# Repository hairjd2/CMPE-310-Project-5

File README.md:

# CMPE-310-Project-5
## Created by Seth Ellis and John Hair (CMPE-306 Failers)

### Design

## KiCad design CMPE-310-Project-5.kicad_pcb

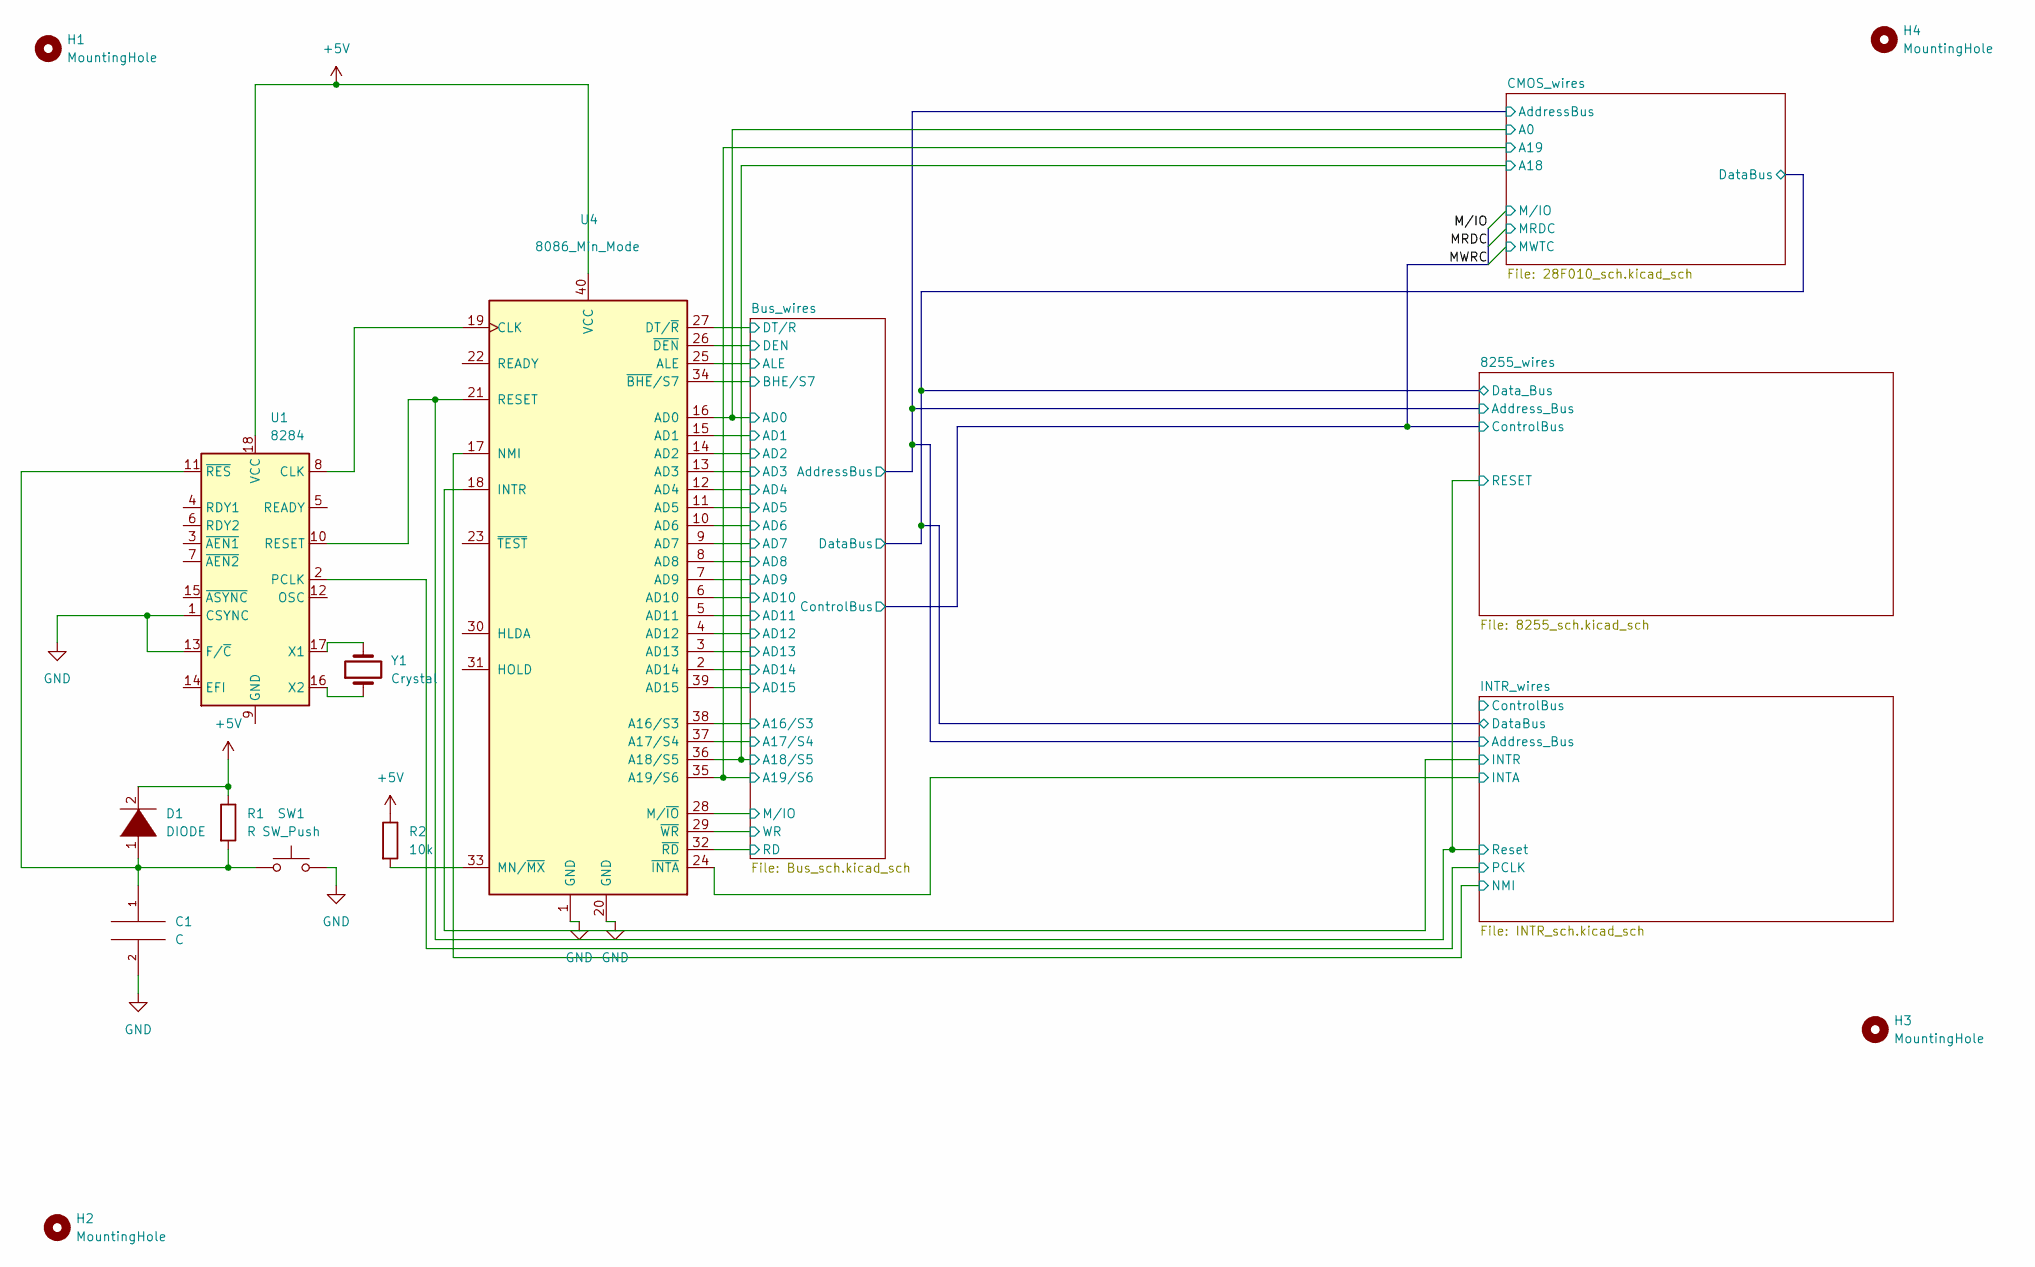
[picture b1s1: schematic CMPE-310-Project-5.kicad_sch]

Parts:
C1: C; CP_Elec_3x5.3
D1: DIODE; D_0201_0603Metric
H1, H2, H3, H4: MountingHole
R1: R; R_0201_0603Metric
R2: 10k; R_0201_0603Metric
SW1: SW_Push; SW_Cherry_MX_1.00u_PCB
U1: 8284; DIP-18_W7.62mm
U4: 8086_Min_Mode; DIP-40_W15.24mm
Y1: Crystal; Crystal_AT310_D3.0mm_L10.0mm_Horizontal

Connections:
+5V: D1.2 (A), R1.1, R2.1, U1.18 (VCC), U4.40 (VCC); also elsewhere on the board
/8255_wires/RESET: U1.10 (RESET), U4.21 (RESET); also elsewhere on the board
/Bus_wires/A16/S3: U4.38 (A16/S3); also elsewhere on the board
/Bus_wires/A17/S4: U4.37 (A17/S4); also elsewhere on the board
/Bus_wires/AD1: U4.15 (AD1); also elsewhere on the board
/Bus_wires/AD2: U4.14 (AD2); also elsewhere on the board
/Bus_wires/AD3: U4.13 (AD3); also elsewhere on the board
/Bus_wires/AD4: U4.12 (AD4); also elsewhere on the board
/Bus_wires/AD5: U4.11 (AD5); also elsewhere on the board
/Bus_wires/AD6: U4.10 (AD6); also elsewhere on the board
/Bus_wires/AD7: U4.9 (AD7); also elsewhere on the board
/Bus_wires/AD8: U4.8 (AD8); also elsewhere on the board
/Bus_wires/AD9: U4.7 (AD9); also elsewhere on the board
/Bus_wires/AD10: U4.6 (AD10); also elsewhere on the board
/Bus_wires/AD11: U4.5 (AD11); also elsewhere on the board
/Bus_wires/AD12: U4.4 (AD12); also elsewhere on the board
/Bus_wires/AD13: U4.3 (AD13); also elsewhere on the board
/Bus_wires/AD14: U4.2 (AD14); also elsewhere on the board
/Bus_wires/AD15: U4.39 (AD15); also elsewhere on the board
/Bus_wires/ALE: U4.25 (ALE); also elsewhere on the board
/Bus_wires/BHE/S7: U4.34 (~BHE/S7); also elsewhere on the board
/Bus_wires/DEN: U4.26 (~DEN); also elsewhere on the board
/Bus_wires/DT/R: U4.27 (DT/~R); also elsewhere on the board
/Bus_wires/RD: U4.32 (~RD); also elsewhere on the board
/Bus_wires/WR: U4.29 (~WR); also elsewhere on the board
/CMOS_wires/A0: U4.16 (AD0); also elsewhere on the board
/CMOS_wires/A18: U4.36 (A18/S5); also elsewhere on the board
/CMOS_wires/A19: U4.35 (A19/S6); also elsewhere on the board
/INTR_wires/INTA: U4.24 (~INTA); also elsewhere on the board
/INTR_wires/INTR: U4.18 (INTR); also elsewhere on the board
/INTR_wires/NMI: U4.17 (NMI); also elsewhere on the board
/INTR_wires/PCLK: U1.2 (PCLK); also elsewhere on the board
/MRDC: U4.28 (M/~IO); also elsewhere on the board
GND: C1.2, SW1.2, U1.1 (CSYNC), U1.13 (F/~C), U4.1 (GND), U4.20 (GND); also elsewhere on the board
unnamed: C1.1, D1.1 (K), R1.2, SW1.1, U1.11 (~RES)
unnamed: R2.2, U4.33 (MN/~MX)
unnamed: U1.8 (CLK), U4.19 (CLK)
unnamed: U1.16 (X2), Y1.1
unnamed: U1.17 (X1), Y1.2

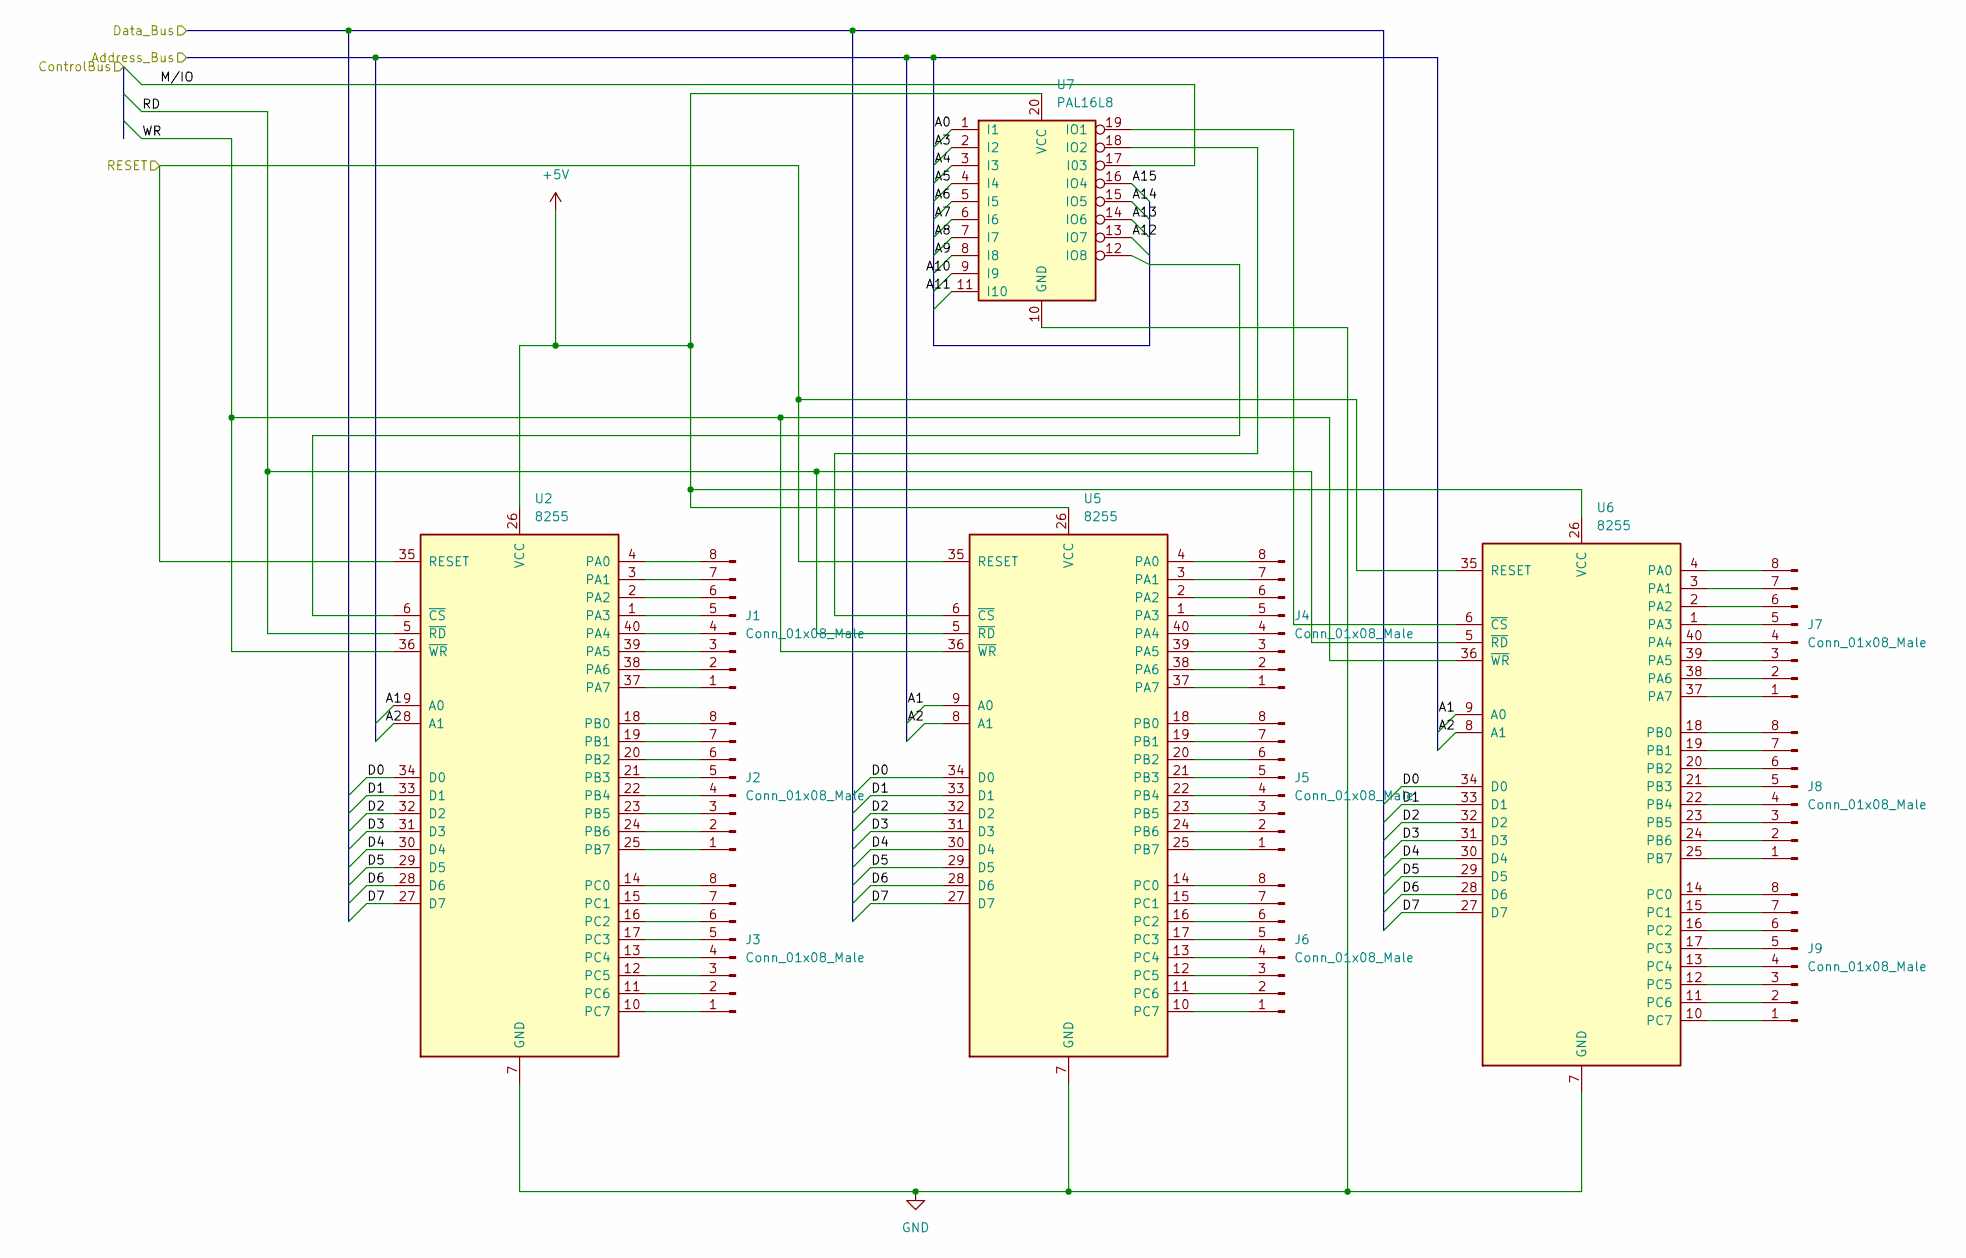
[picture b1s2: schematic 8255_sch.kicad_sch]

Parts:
J1, J2, J3, J4, J5, J6, J7, J8, J9: Conn_01x08_Male; Harwin_M20-89008xx_1x08_P2.54mm_Horizontal
U2, U5, U6: 8255; DIP-40_W15.24mm
U7: PAL16L8; DIP-20_W7.62mm

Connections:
+5V: U2.26 (VCC), U5.26 (VCC), U6.26 (VCC), U7.20 (VCC); also elsewhere on the board
/8255_wires/A0: U7.1 (I1)
/8255_wires/A1: U5.9 (A0), U6.9 (A0)
/8255_wires/A2: U5.8 (A1), U6.8 (A1)
/8255_wires/A3: U7.2 (I2)
/8255_wires/A4: U7.3 (I3)
/8255_wires/A5: U7.4 (I4)
/8255_wires/A6: U7.5 (I5)
/8255_wires/A7: U7.6 (I6)
/8255_wires/A8: U7.7 (I7)
/8255_wires/A9: U7.8 (I8)
/8255_wires/A10: U7.9 (I9)
/8255_wires/A11: U7.11 (I10)
/8255_wires/A12: U7.13 (IO7)
/8255_wires/A13: U7.14 (IO6)
/8255_wires/A14: U7.15 (IO5)
/8255_wires/A15: U7.16 (IO4)
/8255_wires/D0: U2.34 (D0), U5.34 (D0), U6.34 (D0)
/8255_wires/D1: U2.33 (D1), U5.33 (D1), U6.33 (D1)
/8255_wires/D2: U2.32 (D2), U5.32 (D2), U6.32 (D2)
/8255_wires/D3: U2.31 (D3), U5.31 (D3), U6.31 (D3)
/8255_wires/D4: U2.30 (D4), U5.30 (D4), U6.30 (D4)
/8255_wires/D5: U2.29 (D5), U5.29 (D5), U6.29 (D5)
/8255_wires/D6: U2.28 (D6), U5.28 (D6), U6.28 (D6)
/8255_wires/D7: U2.27 (D7), U5.27 (D7), U6.27 (D7)
/8255_wires/M/IO: U7.17 (I03)
/8255_wires/RD: U2.5 (~RD), U5.5 (~RD), U6.5 (~RD)
/8255_wires/RESET: U2.35 (RESET), U5.35 (RESET), U6.35 (RESET); also elsewhere on the board
/8255_wires/WR: U2.36 (~WR), U5.36 (~WR), U6.36 (~WR)
GND: U2.7 (GND), U5.7 (GND), U6.7 (GND), U7.10 (GND); also elsewhere on the board
unnamed: J1.1, U2.37 (PA7)
unnamed: J1.2, U2.38 (PA6)
unnamed: J1.3, U2.39 (PA5)
unnamed: J1.4, U2.40 (PA4)
unnamed: J1.5, U2.1 (PA3)
unnamed: J1.6, U2.2 (PA2)
unnamed: J1.7, U2.3 (PA1)
unnamed: J1.8, U2.4 (PA0)
unnamed: J2.1, U2.25 (PB7)
unnamed: J2.2, U2.24 (PB6)
unnamed: J2.3, U2.23 (PB5)
unnamed: J2.4, U2.22 (PB4)
unnamed: J2.5, U2.21 (PB3)
unnamed: J2.6, U2.20 (PB2)
unnamed: J2.7, U2.19 (PB1)
unnamed: J2.8, U2.18 (PB0)
unnamed: J3.1, U2.10 (PC7)
unnamed: J3.2, U2.11 (PC6)
unnamed: J3.3, U2.12 (PC5)
unnamed: J3.4, U2.13 (PC4)
unnamed: J3.5, U2.17 (PC3)
unnamed: J3.6, U2.16 (PC2)
unnamed: J3.7, U2.15 (PC1)
unnamed: J3.8, U2.14 (PC0)
unnamed: J4.1, U5.37 (PA7)
unnamed: J4.2, U5.38 (PA6)
unnamed: J4.3, U5.39 (PA5)
unnamed: J4.4, U5.40 (PA4)
unnamed: J4.5, U5.1 (PA3)
unnamed: J4.6, U5.2 (PA2)
unnamed: J4.7, U5.3 (PA1)
unnamed: J4.8, U5.4 (PA0)
unnamed: J5.1, U5.25 (PB7)
unnamed: J5.2, U5.24 (PB6)
unnamed: J5.3, U5.23 (PB5)
unnamed: J5.4, U5.22 (PB4)
unnamed: J5.5, U5.21 (PB3)
unnamed: J5.6, U5.20 (PB2)
unnamed: J5.7, U5.19 (PB1)
unnamed: J5.8, U5.18 (PB0)
unnamed: J6.1, U5.10 (PC7)
unnamed: J6.2, U5.11 (PC6)
unnamed: J6.3, U5.12 (PC5)
unnamed: J6.4, U5.13 (PC4)
unnamed: J6.5, U5.17 (PC3)
unnamed: J6.6, U5.16 (PC2)
unnamed: J6.7, U5.15 (PC1)
unnamed: J6.8, U5.14 (PC0)
unnamed: J7.1, U6.37 (PA7)
unnamed: J7.2, U6.38 (PA6)
unnamed: J7.3, U6.39 (PA5)
unnamed: J7.4, U6.40 (PA4)
unnamed: J7.5, U6.1 (PA3)
unnamed: J7.6, U6.2 (PA2)
unnamed: J7.7, U6.3 (PA1)
unnamed: J7.8, U6.4 (PA0)
unnamed: J8.1, U6.25 (PB7)
unnamed: J8.2, U6.24 (PB6)
unnamed: J8.3, U6.23 (PB5)
unnamed: J8.4, U6.22 (PB4)
unnamed: J8.5, U6.21 (PB3)
unnamed: J8.6, U6.20 (PB2)
unnamed: J8.7, U6.19 (PB1)
unnamed: J8.8, U6.18 (PB0)
unnamed: J9.1, U6.10 (PC7)
unnamed: J9.2, U6.11 (PC6)
unnamed: J9.3, U6.12 (PC5)
unnamed: J9.4, U6.13 (PC4)
unnamed: J9.5, U6.17 (PC3)
unnamed: J9.6, U6.16 (PC2)
unnamed: J9.7, U6.15 (PC1)
unnamed: J9.8, U6.14 (PC0)
unnamed: U2.6 (~CS), U7.12 (IO8)
unnamed: U5.6 (~CS), U7.18 (IO2)
unnamed: U6.6 (~CS), U7.19 (IO1)

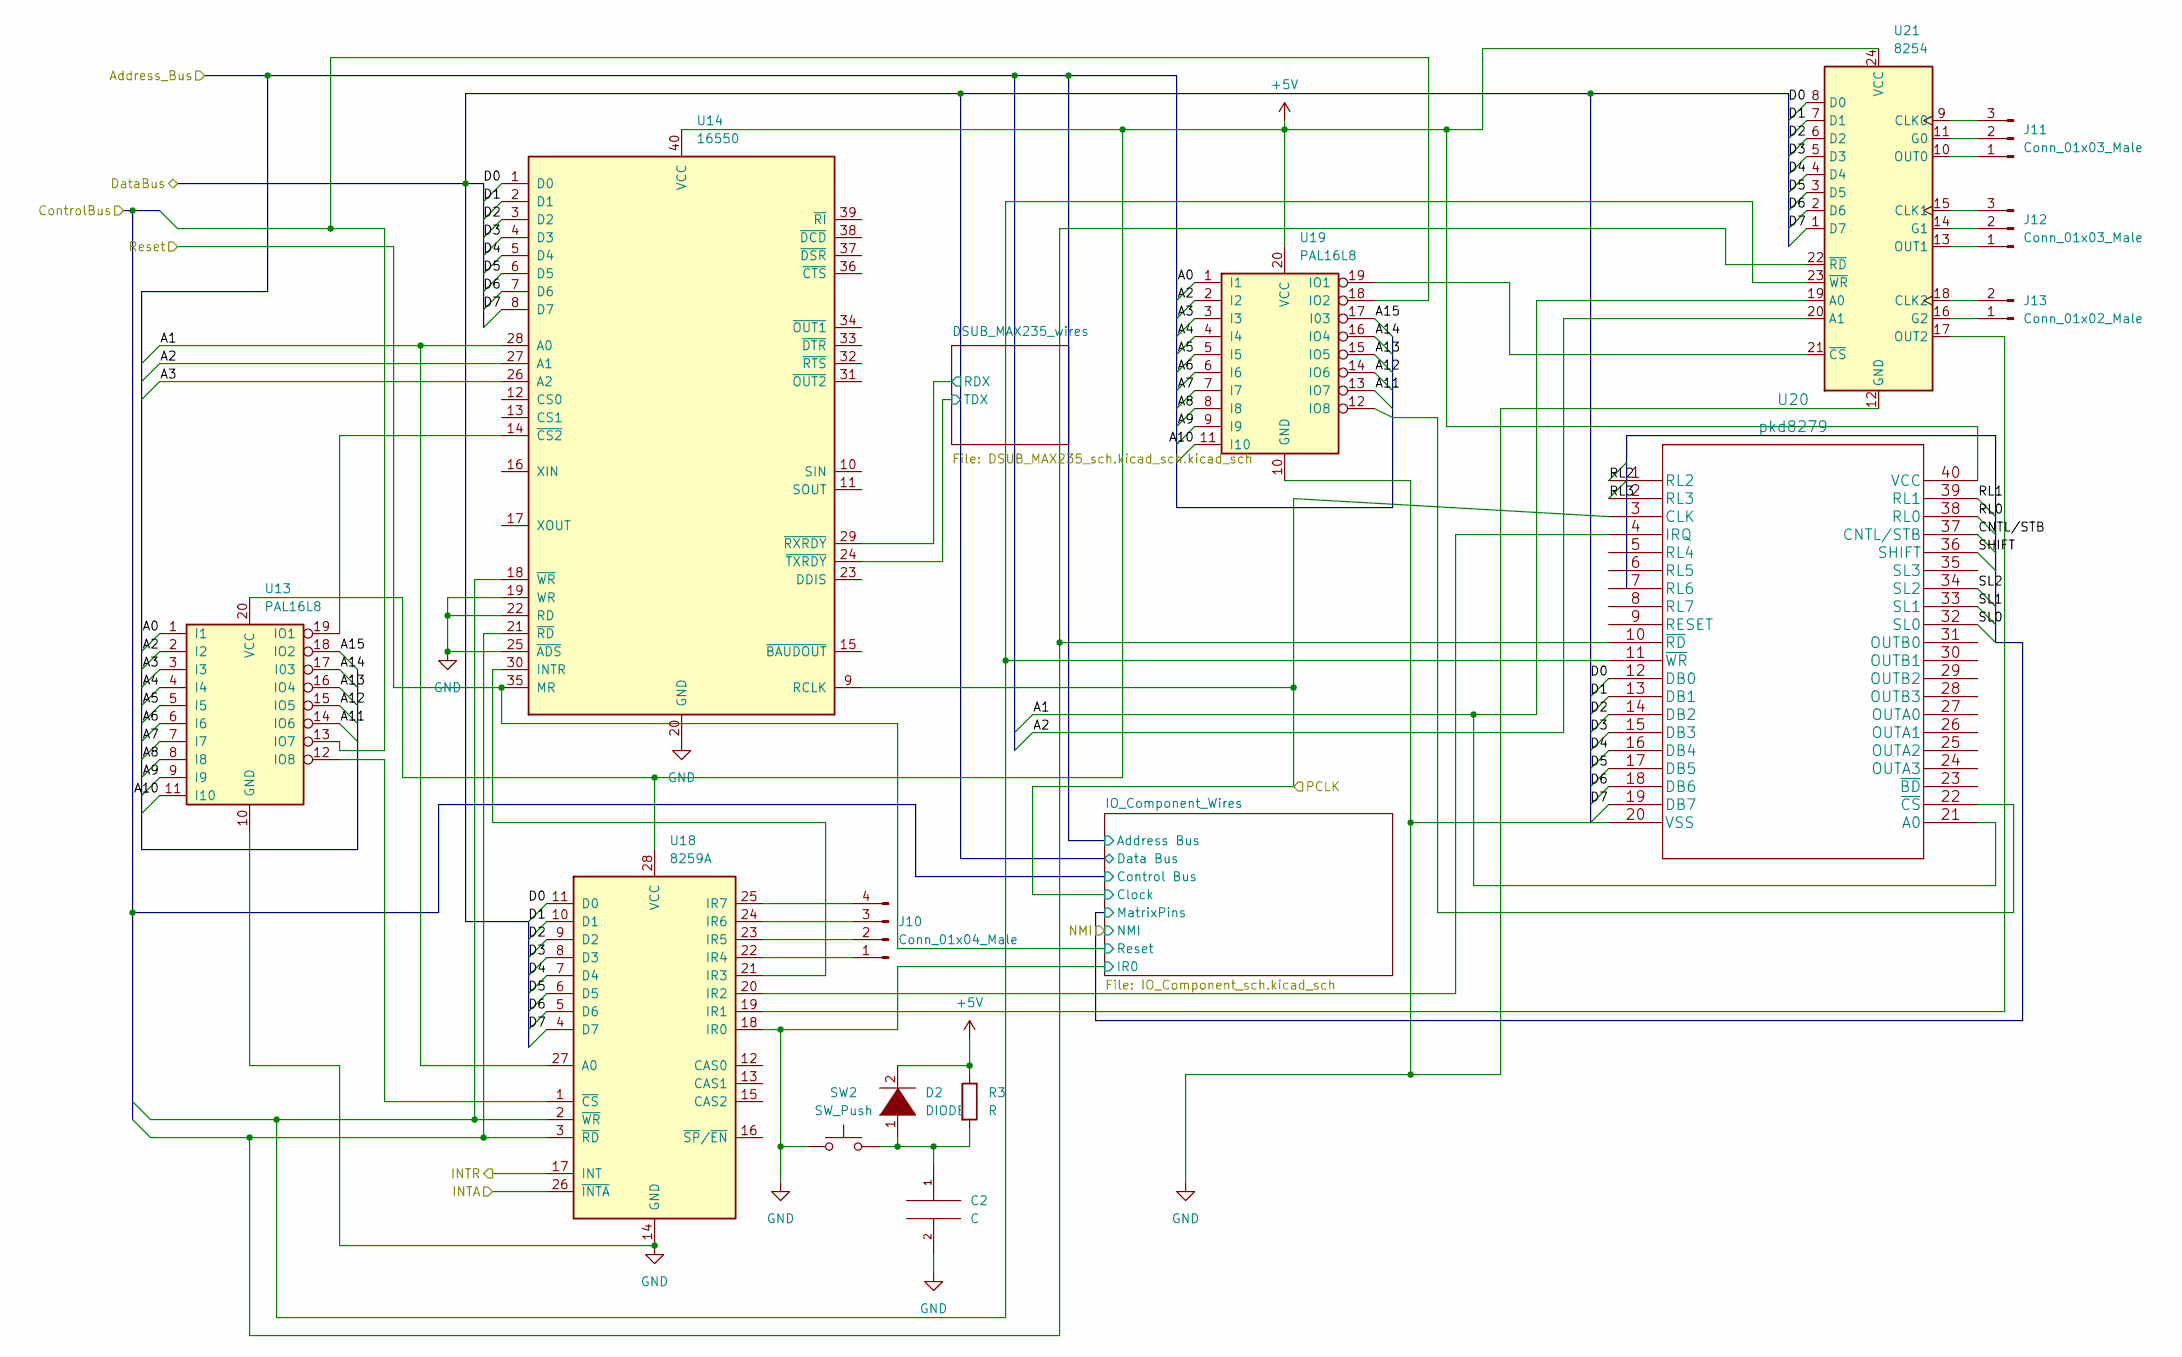
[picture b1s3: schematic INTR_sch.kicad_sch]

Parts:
C2: C; CP_Elec_3x5.3
D2: DIODE; D_0201_0603Metric
J10: Conn_01x04_Male; Harwin_M20-89008xx_1x08_P2.54mm_Horizontal
J11, J12: Conn_01x03_Male; Harwin_M20-89008xx_1x08_P2.54mm_Horizontal
J13: Conn_01x02_Male; Harwin_M20-89008xx_1x08_P2.54mm_Horizontal
R3: R; R_0201_0603Metric
SW2: SW_Push; SW_Cherry_MX_1.00u_PCB
U13, U19: PAL16L8; DIP-20_W7.62mm
U14: 16550; DIP-40_W15.24mm
U18: 8259A; DIP-28_W15.24mm
U20: pkd8279
U21: 8254; DIP-24_W15.24mm

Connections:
+5V: D2.2 (A), R3.1, U13.20 (VCC), U14.40 (VCC), U18.28 (VCC), U19.20 (VCC), U20.40 (VCC), U21.24 (VCC); also elsewhere on the board
/8255_wires/RESET: U14.35 (MR); also elsewhere on the board
/INTR_wires/A0: U13.1 (I1), U19.1 (I1)
/INTR_wires/A1: U14.28 (A0), U18.27 (A0), U20.21 (A0), U21.19 (A0)
/INTR_wires/A2: U13.2 (I2), U14.27 (A1), U19.2 (I2), U21.20 (A1)
/INTR_wires/A3: U13.3 (I3), U14.26 (A2), U19.3 (I3)
/INTR_wires/A4: U13.4 (I4), U19.4 (I4)
/INTR_wires/A5: U13.5 (I5), U19.5 (I5)
/INTR_wires/A6: U13.6 (I6), U19.6 (I6)
/INTR_wires/A7: U13.7 (I7), U19.7 (I7)
/INTR_wires/A8: U13.8 (I8), U19.8 (I8)
/INTR_wires/A9: U13.9 (I9), U19.9 (I9)
/INTR_wires/A10: U13.11 (I10), U19.11 (I10)
/INTR_wires/A11: U13.14 (IO6), U19.13 (IO7)
/INTR_wires/A12: U13.15 (IO5), U19.14 (IO6)
/INTR_wires/A13: U13.16 (IO4), U19.15 (IO5)
/INTR_wires/A14: U13.17 (I03), U19.16 (IO4)
/INTR_wires/A15: U13.18 (IO2), U19.17 (I03)
/INTR_wires/CNTL/STB: U20.37 (CNTL/STB)
/INTR_wires/D0: U14.1 (D0), U18.11 (D0), U20.12 (DB0), U21.8 (D0)
/INTR_wires/D1: U14.2 (D1), U18.10 (D1), U20.13 (DB1), U21.7 (D1)
/INTR_wires/D2: U14.3 (D2), U18.9 (D2), U20.14 (DB2), U21.6 (D2)
/INTR_wires/D3: U14.4 (D3), U18.8 (D3), U20.15 (DB3), U21.5 (D3)
/INTR_wires/D4: U14.5 (D4), U18.7 (D4), U20.16 (DB4), U21.4 (D4)
/INTR_wires/D5: U14.6 (D5), U18.6 (D5), U20.17 (DB5), U21.3 (D5)
/INTR_wires/D6: U14.7 (D6), U18.5 (D6), U20.18 (DB6), U21.2 (D6)
/INTR_wires/D7: U14.8 (D7), U18.4 (D7), U20.19 (DB7), U21.1 (D7)
/INTR_wires/DSUB_MAX235_wires/RDX: U14.29 (~RXRDY); also elsewhere on the board
/INTR_wires/DSUB_MAX235_wires/TDX: U14.24 (~TXRDY); also elsewhere on the board
/INTR_wires/INTA: U18.26 (~INTA); also elsewhere on the board
/INTR_wires/INTR: U18.17 (INT); also elsewhere on the board
/INTR_wires/PCLK: U14.9 (RCLK), U20.3 (CLK); also elsewhere on the board
/INTR_wires/RL0: U20.38 (RL0)
/INTR_wires/RL1: U20.39 (RL1)
/INTR_wires/RL2: U20.1 (RL2)
/INTR_wires/RL3: U20.2 (RL3)
/INTR_wires/SHIFT: U20.36 (SHIFT)
/INTR_wires/SL0: U20.32 (SL0)
/INTR_wires/SL1: U20.33 (SL1)
/INTR_wires/SL2: U20.34 (SL2)
GND: C2.2, SW2.1, U13.10 (GND), U14.19 (WR), U14.20 (GND), U14.22 (RD), U14.25 (~ADS), U18.14 (GND), U18.18 (IR0), U19.10 (GND), U20.20 (VSS), U21.12 (GND); also elsewhere on the board
unnamed: C2.1, D2.1 (K), R3.2, SW2.2
unnamed: J10.1, U18.22 (IR4)
unnamed: J10.2, U18.23 (IR5)
unnamed: J10.3, U18.24 (IR6)
unnamed: J10.4, U18.25 (IR7)
unnamed: J11.1, U21.10 (OUT0)
unnamed: J11.2, U21.11 (G0)
unnamed: J11.3, U21.9 (CLK0)
unnamed: J12.1, U21.13 (OUT1)
unnamed: J12.2, U21.14 (G1)
unnamed: J12.3, U21.15 (CLK1)
unnamed: J13.1, U21.16 (G2)
unnamed: J13.2, U21.18 (CLK2)
unnamed: U13.12 (IO8), U18.1 (~CS)
unnamed: U13.13 (IO7), U19.18 (IO2)
unnamed: U13.19 (IO1), U14.14 (~CS2)
unnamed: U14.18 (~WR), U18.2 (~WR), U20.11 (~WR), U21.23 (~WR)
unnamed: U14.21 (~RD), U18.3 (~RD), U20.10 (~RD), U21.22 (~RD)
unnamed: U14.30 (INTR), U18.21 (IR3)
unnamed: U18.19 (IR1), U21.17 (OUT2)
unnamed: U18.20 (IR2), U20.4 (IRQ)
unnamed: U19.12 (IO8), U20.22 (~CS)
unnamed: U19.19 (IO1), U21.21 (~CS)

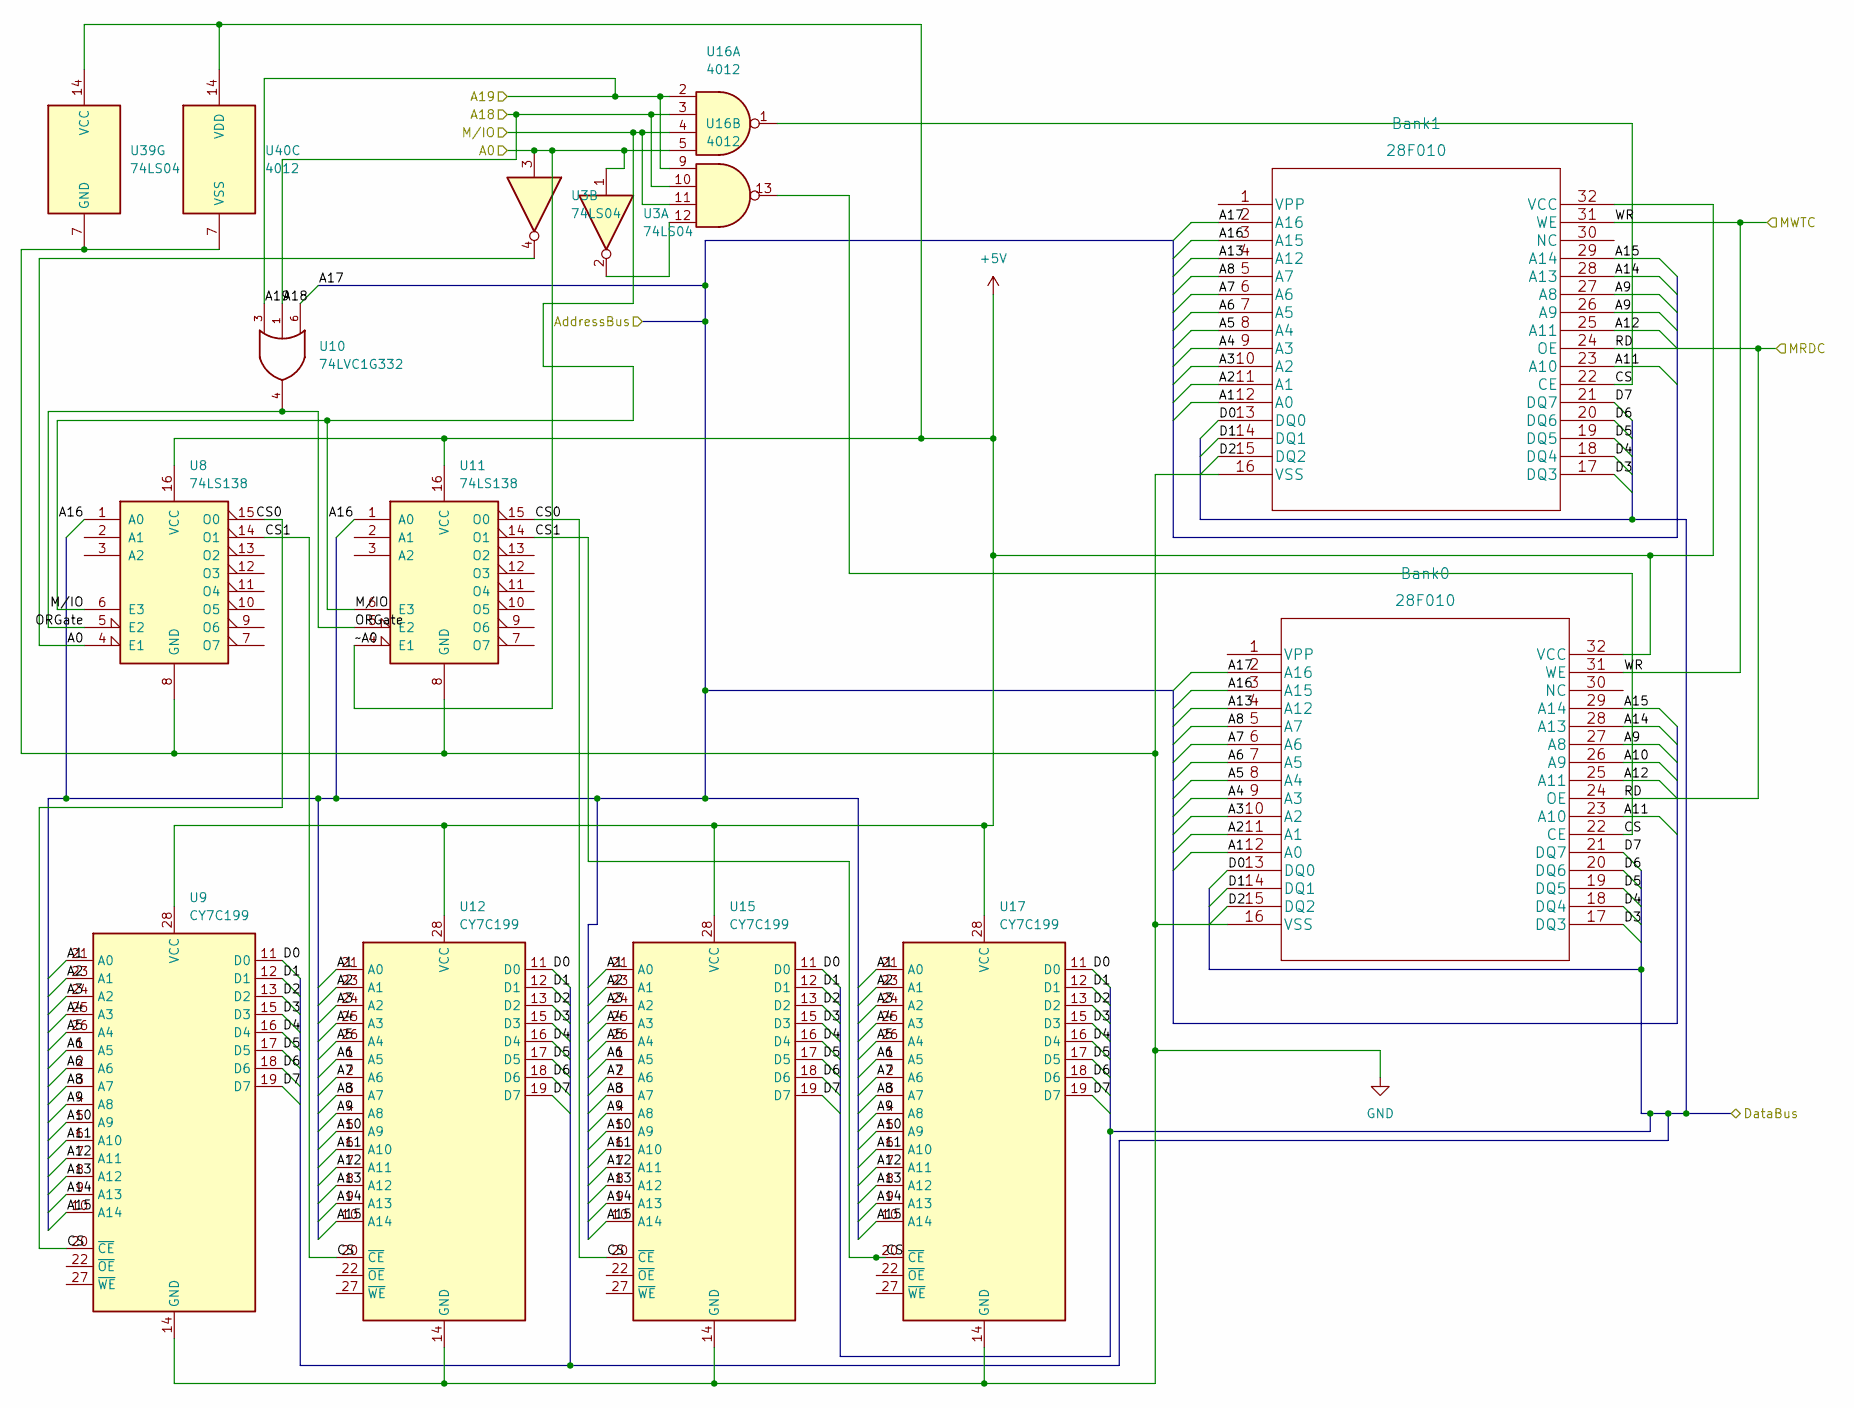
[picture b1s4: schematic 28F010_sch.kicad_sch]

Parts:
Bank0, Bank1: 28F010
U3, U39: 74LS04; DIP-14_W7.62mm
U8, U11: 74LS138; DIP-16_W7.62mm
U9, U12, U15, U17: CY7C199; DIP-28_W7.62mm
U10: 74LVC1G332; SOT-23-6
U16: 4012
U40: 4012; DIP-12_W7.62mm

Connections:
+5V: Bank0.32 (VCC), Bank1.32 (VCC), U8.16 (VCC), U9.28 (VCC), U11.16 (VCC), U12.28 (VCC), U15.28 (VCC), U17.28 (VCC), U39.14 (VCC), U40.14 (VDD); also elsewhere on the board
/CMOS_wires/A0: U3.1, U3.3, U3.4, U8.4 (E1), U11.4 (E1), U16.5; also elsewhere on the board
/CMOS_wires/A1: Bank0.12 (A0), Bank1.12 (A0), U9.21 (A0), U12.21 (A0), U15.21 (A0), U17.21 (A0)
/CMOS_wires/A2: Bank0.11 (A1), Bank1.11 (A1), U9.23 (A1), U12.23 (A1), U15.23 (A1), U17.23 (A1)
/CMOS_wires/A3: Bank0.10 (A2), Bank1.10 (A2), U9.24 (A2), U12.24 (A2), U15.24 (A2), U17.24 (A2)
/CMOS_wires/A4: Bank0.9 (A3), Bank1.9 (A3), U9.25 (A3), U12.25 (A3), U15.25 (A3), U17.25 (A3)
/CMOS_wires/A5: Bank0.8 (A4), Bank1.8 (A4), U9.26 (A4), U12.26 (A4), U15.26 (A4), U17.26 (A4)
/CMOS_wires/A6: Bank0.7 (A5), Bank1.7 (A5), U9.1 (A5), U9.2 (A6), U12.1 (A5), U15.1 (A5), U17.1 (A5)
/CMOS_wires/A7: Bank0.6 (A6), Bank1.6 (A6), U12.2 (A6), U15.2 (A6), U17.2 (A6)
/CMOS_wires/A8: Bank0.5 (A7), Bank1.5 (A7), U9.3 (A7), U12.3 (A7), U15.3 (A7), U17.3 (A7)
/CMOS_wires/A9: Bank0.27 (A8), Bank1.26 (A9), Bank1.27 (A8), U9.4 (A8), U12.4 (A8), U15.4 (A8), U17.4 (A8)
/CMOS_wires/A10: Bank0.26 (A9), U9.5 (A9), U12.5 (A9), U15.5 (A9), U17.5 (A9)
/CMOS_wires/A11: Bank0.23 (A10), Bank1.23 (A10), U9.6 (A10), U12.6 (A10), U15.6 (A10), U17.6 (A10)
/CMOS_wires/A12: Bank0.25 (A11), Bank1.25 (A11), U9.7 (A11), U12.7 (A11), U15.7 (A11), U17.7 (A11)
/CMOS_wires/A13: Bank0.4 (A12), Bank1.4 (A12), U9.8 (A12), U12.8 (A12), U15.8 (A12), U17.8 (A12)
/CMOS_wires/A14: Bank0.28 (A13), Bank1.28 (A13), U9.9 (A13), U12.9 (A13), U15.9 (A13), U17.9 (A13)
/CMOS_wires/A15: Bank0.29 (A14), Bank1.29 (A14), U9.10 (A14), U12.10 (A14), U15.10 (A14), U17.10 (A14)
/CMOS_wires/A16: Bank0.3 (A15), Bank1.3 (A15), U8.1 (A0), U11.1 (A0)
/CMOS_wires/A17: Bank0.2 (A16), Bank1.2 (A16)
/CMOS_wires/A18: U10.1, U16.3, U16.10; also elsewhere on the board
/CMOS_wires/A19: U10.3, U16.2, U16.9; also elsewhere on the board
/CMOS_wires/CS: Bank0.22 (CE), Bank1.22 (CE), U8.14 (O1), U8.15 (O0), U9.20 (~CE), U11.14 (O1), U11.15 (O0), U12.20 (~CE), U15.20 (~CE), U16.1, U16.13, U17.20 (~CE)
/CMOS_wires/D0: Bank0.13 (DQ0), Bank1.13 (DQ0), U9.11 (D0), U12.11 (D0), U15.11 (D0), U17.11 (D0)
/CMOS_wires/D1: Bank0.14 (DQ1), Bank1.14 (DQ1), U9.12 (D1), U12.12 (D1), U15.12 (D1), U17.12 (D1)
/CMOS_wires/D2: Bank0.15 (DQ2), Bank1.15 (DQ2), U9.13 (D2), U12.13 (D2), U15.13 (D2), U17.13 (D2)
/CMOS_wires/D3: Bank0.17 (DQ3), Bank1.17 (DQ3), U9.15 (D3), U12.15 (D3), U15.15 (D3), U17.15 (D3)
/CMOS_wires/D4: Bank0.18 (DQ4), Bank1.18 (DQ4), U9.16 (D4), U12.16 (D4), U15.16 (D4), U17.16 (D4)
/CMOS_wires/D5: Bank0.19 (DQ5), Bank1.19 (DQ5), U9.17 (D5), U12.17 (D5), U15.17 (D5), U17.17 (D5)
/CMOS_wires/D6: Bank0.20 (DQ6), Bank1.20 (DQ6), U9.18 (D6), U12.18 (D6), U15.18 (D6), U17.18 (D6)
/CMOS_wires/D7: Bank0.21 (DQ7), Bank1.21 (DQ7), U9.19 (D7), U12.19 (D7), U15.19 (D7), U17.19 (D7)
/CMOS_wires/M/IO: U8.6 (E3), U11.6 (E3), U16.4, U16.11
/CMOS_wires/ORGate: U8.5 (E2), U10.4, U11.5 (E2)
/CMOS_wires/RD: Bank0.24 (OE), Bank1.24 (OE)
/CMOS_wires/WR: Bank0.31 (WE), Bank1.31 (WE)
GND: Bank0.16 (VSS), Bank1.16 (VSS), U8.8 (GND), U9.14 (GND), U10.2 (GND), U11.8 (GND), U12.14 (GND), U15.14 (GND), U17.14 (GND), U39.7 (GND), U40.7 (VSS); also elsewhere on the board
unnamed: U3.2, U16.12
VCC: U10.5 (VCC)

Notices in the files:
parts and their libraries:
Copyright 2016 Accelerated Designs. All rights reserved.
